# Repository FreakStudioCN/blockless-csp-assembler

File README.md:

# Blockless PCB Studio

Turn a product brief into a modular PCB backplane concept, then inspect the module plan, placement, routing, enclosure, BOM, checks, and manufacturing-oriented outputs in one workspace.

[Apache-2.0 licensed](LICENSE) · English UI by default · Chinese UI included

## Investor presentation

The roadshow/investor presentation is available as a static HTML deck:

- GitHub Pages: <https://freakstudiocn.github.io/blockless-csp-assembler/presentation.html>
- Backup preview: <https://htmlpreview.github.io/?https://github.com/FreakStudioCN/blockless-csp-assembler/blob/main/presentation.html>
- Local file: [`presentation.html`](presentation.html)

GitHub Pages setup for this repository:

1. Open the repository on GitHub, then go to **Settings** -> **Pages**.
2. Under **Build and deployment**, set **Source** to **Deploy from a branch**.
3. Set **Branch** to `main` and the folder to `/(root)`, then click **Save**.

## What it does

Blockless PCB Studio is a browser-based prototype for building products from reviewed commercial modules instead of redesigning every circuit from scratch.

The browser workspace can:

- match a natural-language brief to one of 13 curated product cases;
- select compatible ESP32, sensor, radio, power, display, storage, and connector modules;
- generate deterministic placement constraints, keepouts, nets, and an editable routing sketch;
- preview the board and a generated enclosure in 2D and 3D;
- export a BOM, review report, module-asset manifest, OpenSCAD enclosure, and a structured JLC EDA-oriented ZIP;
- display cached KiCad/KiCadRoutingTools outputs and CAM/CNC previews.

The optional KiCad host flow goes further: it creates real `.kicad_pcb` files, routes copper with KiCadRoutingTools, runs KiCad DRC, exports layer SVGs, renders the board, and can generate pcb2gcode CNC toolpaths.

## Important scope boundary

This repository is an MVP, not a general-purpose or fabrication-ready AI PCB designer.

- The current browser planner does not call an LLM. It scores the prompt against 13 curated cases and applies deterministic module, placement, and routing rules.
- The interactive browser routes are design sketches. The KiCad host flow is the source of real copper geometry.
- Browser-side net, trace-width, and clearance entries describe design intent or preview geometry; they are not KiCad ERC/DRC results. KiCad ERC/DRC remains authoritative.
- The JLC EDA export is a structured demo subset, not a native production project.
- The checked-in `*-krt-drc.rpt` reports show 0 DRC violations and 0 unconnected pads for the two routed demos. The pre-routing reports intentionally show unresolved connectivity, and several checks in the routed reports are excluded. Always review the board, footprints, rules, and manufacturing outputs before fabrication.

## Quick start

Requirements:

- Node.js 22 or newer
- npm 10 or newer

```powershell
git clone https://github.com/FreakStudioCN/blockless-csp-assembler.git
cd blockless-csp-assembler
npm ci
npm run dev -- --port 5173
```

Open <http://127.0.0.1:5173>.

### Docker Desktop

For a browser-only demo on Windows or macOS:

```powershell
docker compose up --build
```

Open <http://127.0.0.1:5173>. Native KiCad and CAM actions are disabled in the container.

The real CAD assets and generated demo outputs needed by the UI are already cached in the repository. To refresh public module assets from their upstream sources:

```powershell
npm run harvest:assets
```

## How it works

```text
Product brief
    -> curated case matching
    -> commercial module selection
    -> interface and net matching
    -> constraint-based placement
    -> interactive A* routing sketch
    -> BOM / checks / enclosure / export

Optional native host flow
    -> plan JSON
    -> KiCad board synthesis
    -> KiCadRoutingTools autorouting
    -> KiCad DRC / SVG / 3D render
    -> pcb2gcode CAM output
```

The AI boundary is deliberately narrow: language models can propose module choices and constraints, while deterministic tools own geometry, routing, and verification.

## Demo cases

The browser contains 13 curated briefs. Two have complete checked-in KiCad host outputs:

- Long-range battery-powered environmental node: ESP32, LoRa, BME280/SHT31, LiPo charging, battery connector, and I2C expansion.
- Desktop air-quality monitor: ESP32, SGP30, BME280, OLED, USB-C power, and I2C expansion.

## KiCad host flow

The host scripts support KiCad 10 on Windows and macOS. macOS support covers board generation, KiCadRoutingTools, DRC, rendering, and SVG export; CNC export remains Windows-only. See [`kicad-host-mvp/README.md`](kicad-host-mvp/README.md) for setup details.

Check that KiCad was detected, then download the pinned optional autorouter and its dependencies into ignored local directories:

```powershell
npm run kicad:check
npm run kicad:setup-router
```

```powershell
npm run kicad:plans
npm run kicad:validate
npm run kicad:build
npm run kicad:ai-route
```

Check the local installation first:

```powershell
powershell -ExecutionPolicy Bypass -File .\kicad-host-mvp\scripts\check_kicad.ps1
```

## Verification

The default checks do not require KiCad:

```powershell
npm run build
npm run kicad:validate
npm run test:ui
```

To include the real KiCad + pcb2gcode action in the desktop end-to-end test:

```powershell
$env:RUN_KICAD_INTEGRATION = "1"
npm run test:ui
```

## Repository map

```text
src/                    React workspace and deterministic planning engine
public/assets/          Cached CAD, screenshots, KiCad SVGs, and CAM previews
kicad-host-mvp/         KiCad plugin, plans, scripts, routed boards, and reports
tools/                  Optional local KiCadRoutingTools checkout and dependencies (ignored)
tests/                  Desktop and mobile Playwright flow
docs/media/             README and release media
```

## Known limitations

- Only the two primary demo cases have a complete checked-in KiCad host pipeline.
- Native KiCad automation is exercised locally on Windows. The cross-platform entry point and Web app run in macOS CI, but the full KiCad GUI/render pipeline still needs confirmation on a physical Mac.
- The production JavaScript bundle is about 946 kB before gzip; Three.js and export code should eventually be split into lazy-loaded chunks.
- Module metadata, pin maps, purchase links, and CAD provenance need continued human review as the registry grows.

## License and third-party work

Blockless PCB Studio is licensed under the [Apache License 2.0](LICENSE). Bundled Adafruit CAD assets and the optional KiCadRoutingTools dependency remain under their MIT licenses; see [THIRD_PARTY_NOTICES.md](THIRD_PARTY_NOTICES.md).

## Safety

Do not send generated boards or CNC toolpaths directly to fabrication or a machine. Review electrical rules, footprints, clearances, stack-up, tool diameters, feeds, speeds, workholding, and machine limits first.

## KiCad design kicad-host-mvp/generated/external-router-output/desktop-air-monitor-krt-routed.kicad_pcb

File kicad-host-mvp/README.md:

# KiCad Host MVP

This folder turns the React concept demo into a KiCad-hosted MVP.

The direction is:

```text
React AI console -> module plan JSON -> KiCad board synthesis -> KiCadRoutingTools autoroute -> KiCad DRC / 3D viewer
```

Do not keep expanding the React/Three.js app into a fake EDA. KiCad should host the real board editing experience:

- Users drag footprints in KiCad.
- KiCad shows ratsnest, DRC, copper layers, vias, zones, and 3D preview.
- The plugin creates/updates module placements, board outline, tracks, vias, silkscreen notes, and constraints.
- KiCadRoutingTools is the current autorouting backend.
- Freerouting can be added later through DSN/SES when export/import is stable in the local KiCad toolchain.

## Requirements

- KiCad 10 installed on Windows or macOS.
- Python 3 and Git available from the terminal.
- KiCad's bundled Python and `pcbnew` module available inside KiCad.
- KiCad CLI available in the standard installation location, or configured with `KICAD_CLI` and `KICAD_PYTHON`.
- `npm run kicad:setup-router` downloads a pinned KiCadRoutingTools revision into the ignored `tools/KiCadRoutingTools` directory.
- For CNC export only: `pcb2gcode.exe` available on `PATH`, or its full path set in `PCB2GCODE_EXE`.

This repo can generate plan JSON without KiCad. The plugin itself must run inside KiCad PCB Editor.

## Files

```text
kicad-host-mvp/
  plans/
    long-range-env-node.json
    desktop-air-monitor.json
  plugin/
    ai_modular_backplane/
      __init__.py
      action_plugin.py
      board_builder.py
  scripts/
    generate_plan.py
    install_plugin.ps1
    check_kicad.ps1
```

## Quick Start

Generate/validate plans first:

```powershell
npm run kicad:check
npm run kicad:setup-router
npm run kicad:plans
npm run kicad:validate
npm run kicad:build
npm run kicad:ai-route
```

On macOS, the scripts automatically inspect `/Applications/KiCad/KiCad.app`. CNC export is not supported there. If KiCad is installed elsewhere, set `KICAD_CLI` and `KICAD_PYTHON` to the two executable paths before running the commands.

1. Install KiCad.
2. Copy the plugin into KiCad's scripting plugin folder:

```powershell
powershell -ExecutionPolicy Bypass -File .\kicad-host-mvp\scripts\install_plugin.ps1
```

3. Open KiCad PCB Editor.
4. Use `Tools -> External Plugins -> AI Modular Backplane`.
5. Pick one plan JSON from `kicad-host-mvp/plans`.
6. The plugin creates a real KiCad board with module footprints, pads, copper tracks, vias, labels, and keepouts.

The one-command autorouter flow writes:

```text
kicad-host-mvp/generated/external-router-output/*-krt-routed.kicad_pcb
kicad-host-mvp/generated/*-krt-render.png
kicad-host-mvp/reports/*-krt-route.log
kicad-host-mvp/reports/*-krt-drc.rpt
```

## Current Scope

This is a KiCad-hosted MVP, not a production PCB generator. It uses real KiCad board objects, KRT-generated copper, and color-coded WRL presentation models for clear video capture. The original STEP/STL model paths are still kept in the plans, but the default render favors visual distinction over strict CAD material fidelity. The checked-in KRT-routed reports have 0 DRC violations and 0 unconnected pads, with explicitly listed exclusions; the pre-routing reports still contain the expected unresolved connectivity.

The AI boundary is intentional:

- AI/LLM: module selection, interface matching, placement constraints, keepouts, net priorities, routing parameters, DRC feedback interpretation.
- Autorouter: KiCadRoutingTools Rust A* router writes actual copper.
- Future research path: closed-loop RL/tool-using LLM routing against KiCad DRC, using projects such as PCBWorld and PCBench as references.

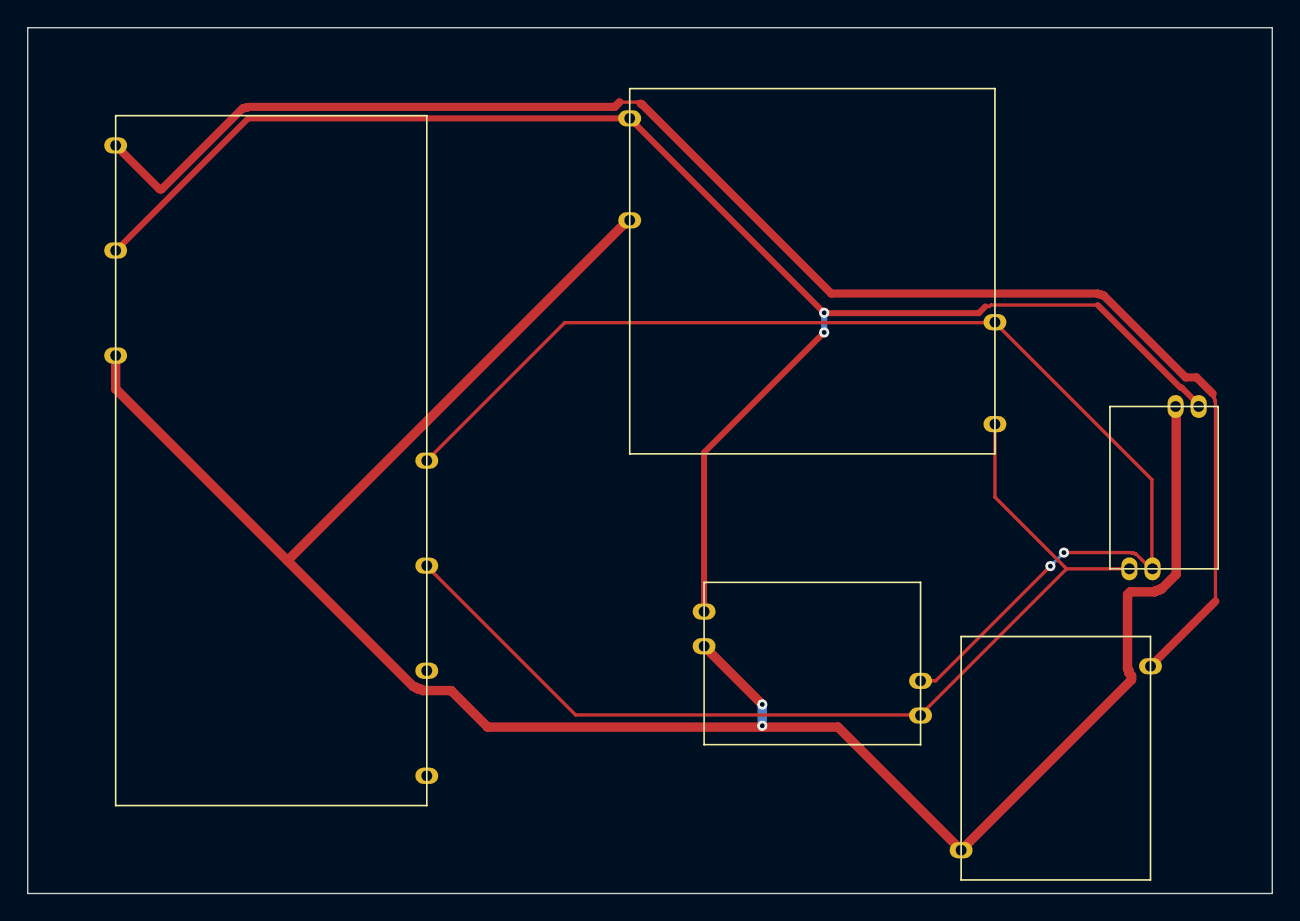
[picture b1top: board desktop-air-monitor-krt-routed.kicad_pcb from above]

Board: 2 copper layers, 92.0 x 64.0 mm, 5 parts (0 on the bottom side), 5 nets.

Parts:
bme280: SGP30/Air Quality I2C Module
esp32-feather: Adafruit HUZZAH32 ESP32 Feather
i2c-expansion: Qwiic/Grove I2C Expansion
oled-128x32: OLED I2C Display
usb-c-5v-breakout: USB-C 5V Power Breakout

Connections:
3V3: bme280.VCC, esp32-feather.3V3, i2c-expansion.VCC, oled-128x32.VCC
5V: esp32-feather.VIN, usb-c-5v-breakout.VBUS
GND: bme280.GND, esp32-feather.GND, i2c-expansion.GND, oled-128x32.GND, usb-c-5v-breakout.GND
I2C_SCL: bme280.SCL, esp32-feather.SCL, i2c-expansion.SCL, oled-128x32.SCL
I2C_SDA: bme280.SDA, esp32-feather.SDA, i2c-expansion.SDA, oled-128x32.SDA

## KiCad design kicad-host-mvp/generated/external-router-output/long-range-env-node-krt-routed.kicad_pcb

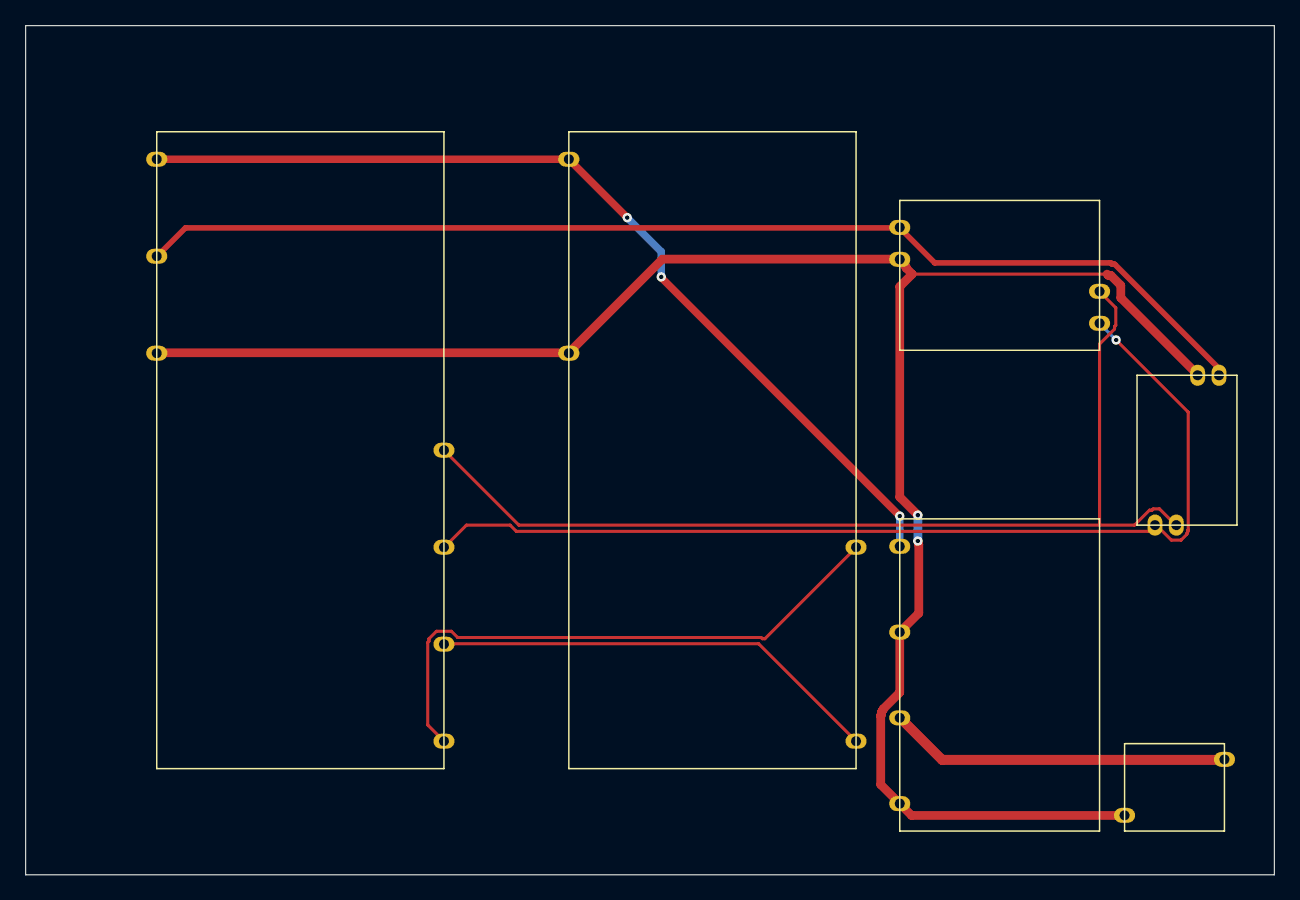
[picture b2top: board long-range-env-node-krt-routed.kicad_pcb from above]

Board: 2 copper layers, 100.0 x 68.0 mm, 6 parts (0 on the bottom side), 8 nets.

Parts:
bme280: Adafruit BME280 I2C
esp32-feather: Adafruit HUZZAH32 ESP32 Feather
i2c-expansion: Qwiic/Grove I2C Expansion
jst-ph-2pin: JST-PH 2Pin Battery Connector
microlipo: Adafruit MicroLipo Charger
radio-featherwing: Adafruit Radio FeatherWing RFM95

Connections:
3V3: bme280.VCC, esp32-feather.3V3, i2c-expansion.VCC
5V: esp32-feather.VIN, microlipo.OUT+, radio-featherwing.VCC
BAT+: jst-ph-2pin.BAT+, microlipo.B+
GND: bme280.GND, esp32-feather.GND, i2c-expansion.GND, jst-ph-2pin.GND, microlipo.B-, microlipo.OUT-, radio-featherwing.GND
I2C_SCL: bme280.SCL, esp32-feather.SCL, i2c-expansion.SCL
I2C_SDA: bme280.SDA, esp32-feather.SDA, i2c-expansion.SDA
LORA_RX: esp32-feather.TX, radio-featherwing.RX
LORA_TX: esp32-feather.RX, radio-featherwing.TX
